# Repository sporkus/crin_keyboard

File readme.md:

# Crin keyboard PCB
-----------

Open sourced replacement PCB for [crin keyboard](https://cannonkeys.com/products/gb-crin-keyboard)

## Fabrication
* verified production files can be found [here](./pcb_production)

## Plate
Plate files can be found here:
https://github.com/cBachoo/bachooKeyboardFiles/tree/master/Crin/CrinPlateFiles

## Misc
#### layout

#### PCB renders

#### Interactive BoM
download this [html](<./documentation/crin custom layout-ibom.html>) and run locally

#### Schematic
[pdf](<./documentation/crin custom layout-schematic.pdf>)

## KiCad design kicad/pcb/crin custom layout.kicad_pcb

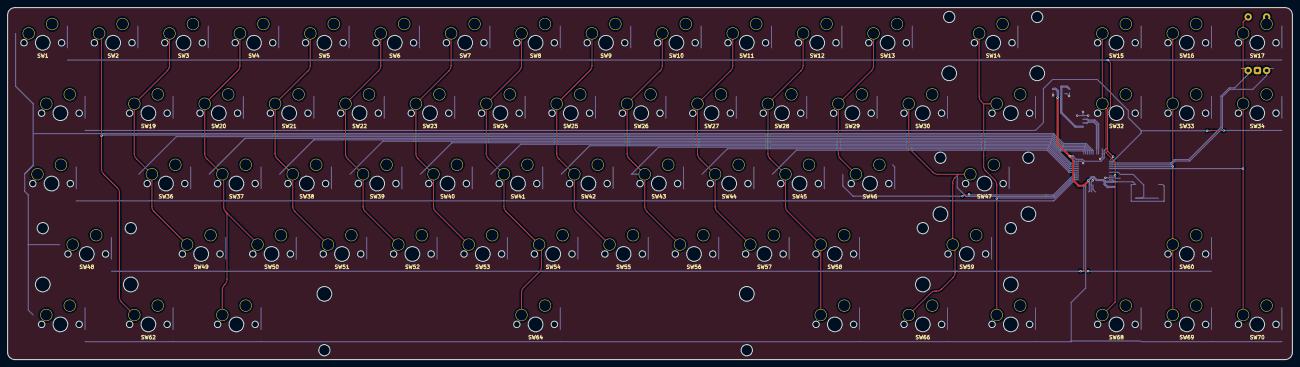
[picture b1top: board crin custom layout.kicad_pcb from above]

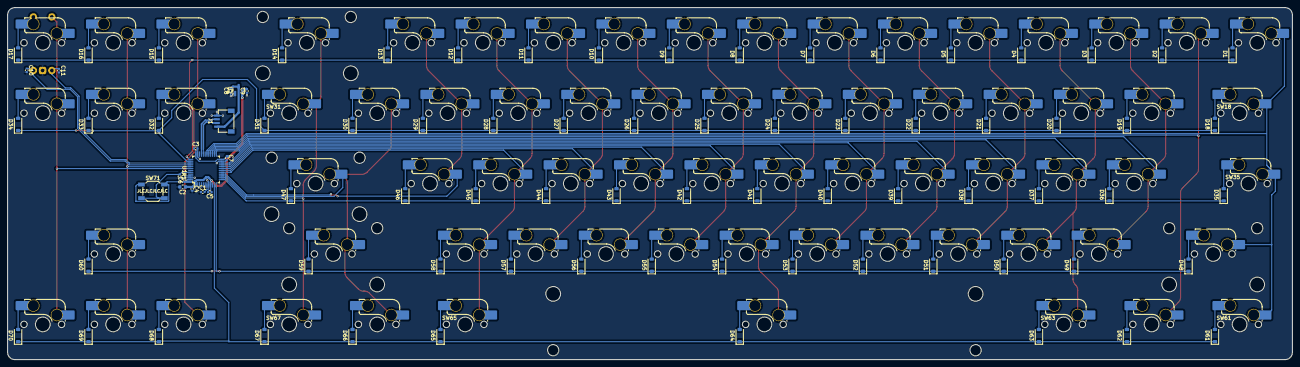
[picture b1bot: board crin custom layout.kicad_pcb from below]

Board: 2 copper layers, 347.7 x 95.2 mm, 157 parts (156 on the bottom side), 102 nets.

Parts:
C1, C3, C4, C5, C6, C7, C10, C11: 100nF; C_0402_1005Metric
C2: 10uF 25V; C_0603_1608Metric
C8, C9: 1uF; C_0402_1005Metric
D1, D2, D3, D4, D5, D6, D7, D8, D9, D10, D11, D12, D13, D14, D15, D16, D17, D18, D19, D20, D21, D22, D23, D24, D25, D26, D27, D28, D29, D30, D31, D32, D33, D34, D35, D36, D37, D38, D39, D40, D41, D42, D43, D44, D45, D46, D47, D48, D49, D50, D51, D52, D53, D54, D55, D56, D57, D58, D59, D60, D61, D62, D63, D64, D65, D66, D67, D68, D69, D70: 1N4148W; D_SOD-123
J1: SM04B-SRSS-TB(LF)(SN); JST-SR-4
R1: 10k; R_0402_1005Metric
SW1, SW2, SW3, SW4, SW5, SW6, SW7, SW8, SW9, SW10, SW11, SW12, SW13, SW14, SW15, SW16, SW17, SW19, SW20, SW21, SW22, SW23, SW24, SW25, SW26, SW27, SW28, SW29, SW30, SW32, SW33, SW34, SW36, SW37, SW38, SW39, SW40, SW41, SW42, SW43, SW44, SW45, SW46, SW47, SW48, SW49, SW50, SW51, SW52, SW53, SW54, SW55, SW56, SW57, SW58, SW59, SW60, SW62, SW64, SW66, SW68, SW69, SW70: MX; SW_MX_HS_1u
SW18, SW31, SW61, SW63, SW65, SW67: MX; SW_MX_HS_1.5u
SW35: MX; SW_MX_HS_1.75u_STP_1.25
SW71: SKQGABE010; SW_SPST_SKQG_WithoutStem
SW73: Rotary_Encoder_Switch; ROT_Alps_EC11E-Switch
U1: STM32F072C8T6; LQFP-48_7x7mm_P0.5mm
U2: XC6206PxxxMR-Regulator_Linear; SOT-23

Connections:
+3V3: C2.1, C3.1, C4.1, C5.1, C6.1, C7.1, C9.2, SW71.1, U1.1 (VBAT), U1.9 (VDDA), U1.24 (VDD), U1.36 (VDDIO2), U1.48 (VDD), U2.2 (VO)
+5V: C8.2, J1.1, U2.3 (VI)
/matrix/COL17_SW: D17.2 (A), SW17.2, SW73.S1
BOOT0: R1.1, SW71.2, U1.44 (BOOT0)
COL0: SW1.1, SW18.1, SW35.1, SW48.1, SW61.1, U1.30 (PA9)
COL1: SW2.1, SW62.1, U1.29 (PA8)
COL2: SW3.1, SW19.1, SW36.1, SW49.1, U1.28 (PB15)
COL3: SW4.1, SW20.1, SW37.1, SW50.1, SW63.1, U1.27 (PB14)
COL4: SW5.1, SW21.1, SW38.1, SW51.1, U1.26 (PB13)
COL5: SW6.1, SW22.1, SW39.1, SW52.1, U1.25 (PB12)
COL6: SW7.1, SW23.1, SW40.1, SW53.1, U1.22 (PB11)
COL7: SW8.1, SW24.1, SW41.1, SW54.1, SW64.1, U1.21 (PB10)
COL8: SW9.1, SW25.1, SW42.1, SW55.1, U1.20 (PB2)
COL9: SW10.1, SW26.1, SW43.1, SW56.1, U1.19 (PB1)
COL10: SW11.1, SW27.1, SW44.1, SW57.1, U1.18 (PB0)
COL11: SW12.1, SW28.1, SW45.1, SW58.1, SW65.1, U1.17 (PA7)
COL12: SW13.1, SW29.1, SW46.1, U1.16 (PA6)
COL13: SW30.1, SW47.1, SW59.1, SW66.1, U1.15 (PA5)
COL14: SW14.1, SW31.1, SW67.1, U1.14 (PA4)
COL15: SW15.1, SW32.1, SW68.1, U1.46 (PB9)
COL16: SW16.1, SW33.1, SW60.1, SW69.1, U1.41 (PB5)
COL17: SW17.1, SW34.1, SW70.1, SW73.S2, U1.42 (PB6)
D_N: J1.2, U1.32 (PA11)
D_P: J1.3, U1.33 (PA12)
ENC_A: C11.1, SW73.A, U1.39 (PB3)
ENC_B: C10.1, SW73.B, U1.40 (PB4)
GND: C1.1, C2.2, C3.2, C4.2, C5.2, C6.2, C7.2, C8.1, C9.1, C10.2, C11.2, J1.4, R1.2, SW73.C, U1.8 (VSSA), U1.23 (VSS), U1.35 (VSS), U1.47 (VSS), U2.1 (GND)
NRST: C1.2, U1.7 (NRST)
unnamed: D1.2 (A), SW1.2
unnamed: D2.2 (A), SW2.2
unnamed: D3.2 (A), SW3.2
unnamed: D4.2 (A), SW4.2
unnamed: D5.2 (A), SW5.2
unnamed: D6.2 (A), SW6.2
unnamed: D7.2 (A), SW7.2
unnamed: D8.2 (A), SW8.2
unnamed: D9.2 (A), SW9.2
unnamed: D10.2 (A), SW10.2
unnamed: D11.2 (A), SW11.2
unnamed: D12.2 (A), SW12.2
unnamed: D13.2 (A), SW13.2
unnamed: D14.2 (A), SW14.2
unnamed: D15.2 (A), SW15.2
unnamed: D16.2 (A), SW16.2
unnamed: D18.2 (A), SW18.2
unnamed: D19.2 (A), SW19.2
unnamed: D20.2 (A), SW20.2
unnamed: D21.2 (A), SW21.2
unnamed: D22.2 (A), SW22.2
unnamed: D23.2 (A), SW23.2
unnamed: D24.2 (A), SW24.2
unnamed: D25.2 (A), SW25.2
unnamed: D26.2 (A), SW26.2
unnamed: D27.2 (A), SW27.2
unnamed: D28.2 (A), SW28.2
unnamed: D29.2 (A), SW29.2
unnamed: D30.2 (A), SW30.2
unnamed: D31.2 (A), SW31.2
unnamed: D32.2 (A), SW32.2
unnamed: D33.2 (A), SW33.2
unnamed: D34.2 (A), SW34.2
unnamed: D35.2 (A), SW35.2
unnamed: D36.2 (A), SW36.2
unnamed: D37.2 (A), SW37.2
unnamed: D38.2 (A), SW38.2
unnamed: D39.2 (A), SW39.2
unnamed: D40.2 (A), SW40.2
unnamed: D41.2 (A), SW41.2
unnamed: D42.2 (A), SW42.2
unnamed: D43.2 (A), SW43.2
unnamed: D44.2 (A), SW44.2
unnamed: D45.2 (A), SW45.2
unnamed: D46.2 (A), SW46.2
unnamed: D47.2 (A), SW47.2
unnamed: D48.2 (A), SW48.2
unnamed: D49.2 (A), SW49.2
unnamed: D50.2 (A), SW50.2
unnamed: D51.2 (A), SW51.2
unnamed: D52.2 (A), SW52.2
unnamed: D53.2 (A), SW53.2
unnamed: D54.2 (A), SW54.2
unnamed: D55.2 (A), SW55.2
unnamed: D56.2 (A), SW56.2
unnamed: D57.2 (A), SW57.2
unnamed: D58.2 (A), SW58.2
unnamed: D59.2 (A), SW59.2
unnamed: D60.2 (A), SW60.2
unnamed: D61.2 (A), SW61.2
unnamed: D62.2 (A), SW62.2
unnamed: D63.2 (A), SW63.2
unnamed: D64.2 (A), SW64.2
unnamed: D65.2 (A), SW65.2
unnamed: D66.2 (A), SW66.2
unnamed: D67.2 (A), SW67.2
unnamed: D68.2 (A), SW68.2
unnamed: D69.2 (A), SW69.2
unnamed: D70.2 (A), SW70.2
ROW0: D1.1 (K), D2.1 (K), D3.1 (K), D4.1 (K), D5.1 (K), D6.1 (K), D7.1 (K), D8.1 (K), D9.1 (K), D10.1 (K), D11.1 (K), D12.1 (K), D13.1 (K), D14.1 (K), D15.1 (K), D16.1 (K), D17.1 (K), U1.37 (PA14)
ROW1: D18.1 (K), D19.1 (K), D20.1 (K), D21.1 (K), D22.1 (K), D23.1 (K), D24.1 (K), D25.1 (K), D26.1 (K), D27.1 (K), D28.1 (K), D29.1 (K), D30.1 (K), D31.1 (K), D32.1 (K), D33.1 (K), D34.1 (K), U1.38 (PA15)
ROW2: D35.1 (K), D36.1 (K), D37.1 (K), D38.1 (K), D39.1 (K), D40.1 (K), D41.1 (K), D42.1 (K), D43.1 (K), D44.1 (K), D45.1 (K), D46.1 (K), D47.1 (K), U1.13 (PA3)
ROW3: D48.1 (K), D49.1 (K), D50.1 (K), D51.1 (K), D52.1 (K), D53.1 (K), D54.1 (K), D55.1 (K), D56.1 (K), D57.1 (K), D58.1 (K), D59.1 (K), D60.1 (K), U1.12 (PA2)
ROW4: D61.1 (K), D62.1 (K), D63.1 (K), D64.1 (K), D65.1 (K), D66.1 (K), D67.1 (K), D68.1 (K), D69.1 (K), D70.1 (K), U1.11 (PA1)

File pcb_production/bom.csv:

Designator,Footprint,Quantity,Value,LCSC Part #
"C1, C10, C11, C3, C4, C5, C6, C7",0402,8,100nF,C307331
C2,0603,1,10uF 25V,
"C8, C9",0402,2,1uF,C52923
"D1, D10, D11, D12, D13, D14, D15, D16, D17, D18, D19, D2, D20, D21, D22, D23, D24, D25, D26, D27, D28, D29, D3, D30, D31, D32, D33, D34, D35, D36, D37, D38, D39, D4, D40, D41, D42, D43, D44, D45, D46, D47, D48, D49, D5, D50, D51, D52, D53, D54, D55, D56, D57, D58, D59, D6, D60, D61, D62, D63, D64, D65, D66, D67, D68, D69, D7, D70, D8, D9",D_SOD-123,70,1N4148W,
J1,JST-SR-4,1,SM04B-SRSS-TB(LF)(SN),
R1,0402,1,10k,
"SW1, SW10, SW11, SW12, SW13, SW14, SW15, SW16, SW17, SW19, SW2, SW20, SW21, SW22, SW23, SW24, SW25, SW26, SW27, SW28, SW29, SW3, SW30, SW32, SW33, SW34, SW36, SW37, SW38, SW39, SW4, SW40, SW41, SW42, SW43, SW44, SW45, SW46, SW47, SW48, SW49, SW5, SW50, SW51, SW52, SW53, SW54, SW55, SW56, SW57, SW58, SW59, SW6, SW60, SW62, SW64, SW66, SW68, SW69, SW7, SW70, SW8, SW9",SW_MX_HS_1u,63,MX,
"SW18, SW31, SW61, SW63, SW65, SW67",SW_MX_HS_1.5u,6,MX,
SW35,SW_MX_HS_1.75u_STP_1.25,1,MX,
SW71,SW_SPST_SKQG_WithoutStem,1,SKQGABE010,
SW73,ROT_Alps_EC11E-Switch,1,Rotary_Encoder_Switch,
U1,LQFP-48_7x7mm_P0.5mm,1,STM32F072C8T6,
U2,SOT-23,1,XC6206PxxxMR-Regulator_Linear,C5446

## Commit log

2023-07-20 init
2023-07-20 fix workflow
2023-07-20 fix doc
2023-08-29 adding firmware files
